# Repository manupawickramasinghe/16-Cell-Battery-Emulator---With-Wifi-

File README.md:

# 16 Cell Battery Emulator - With Wifi 
 Battery Emulator FOr research and testing

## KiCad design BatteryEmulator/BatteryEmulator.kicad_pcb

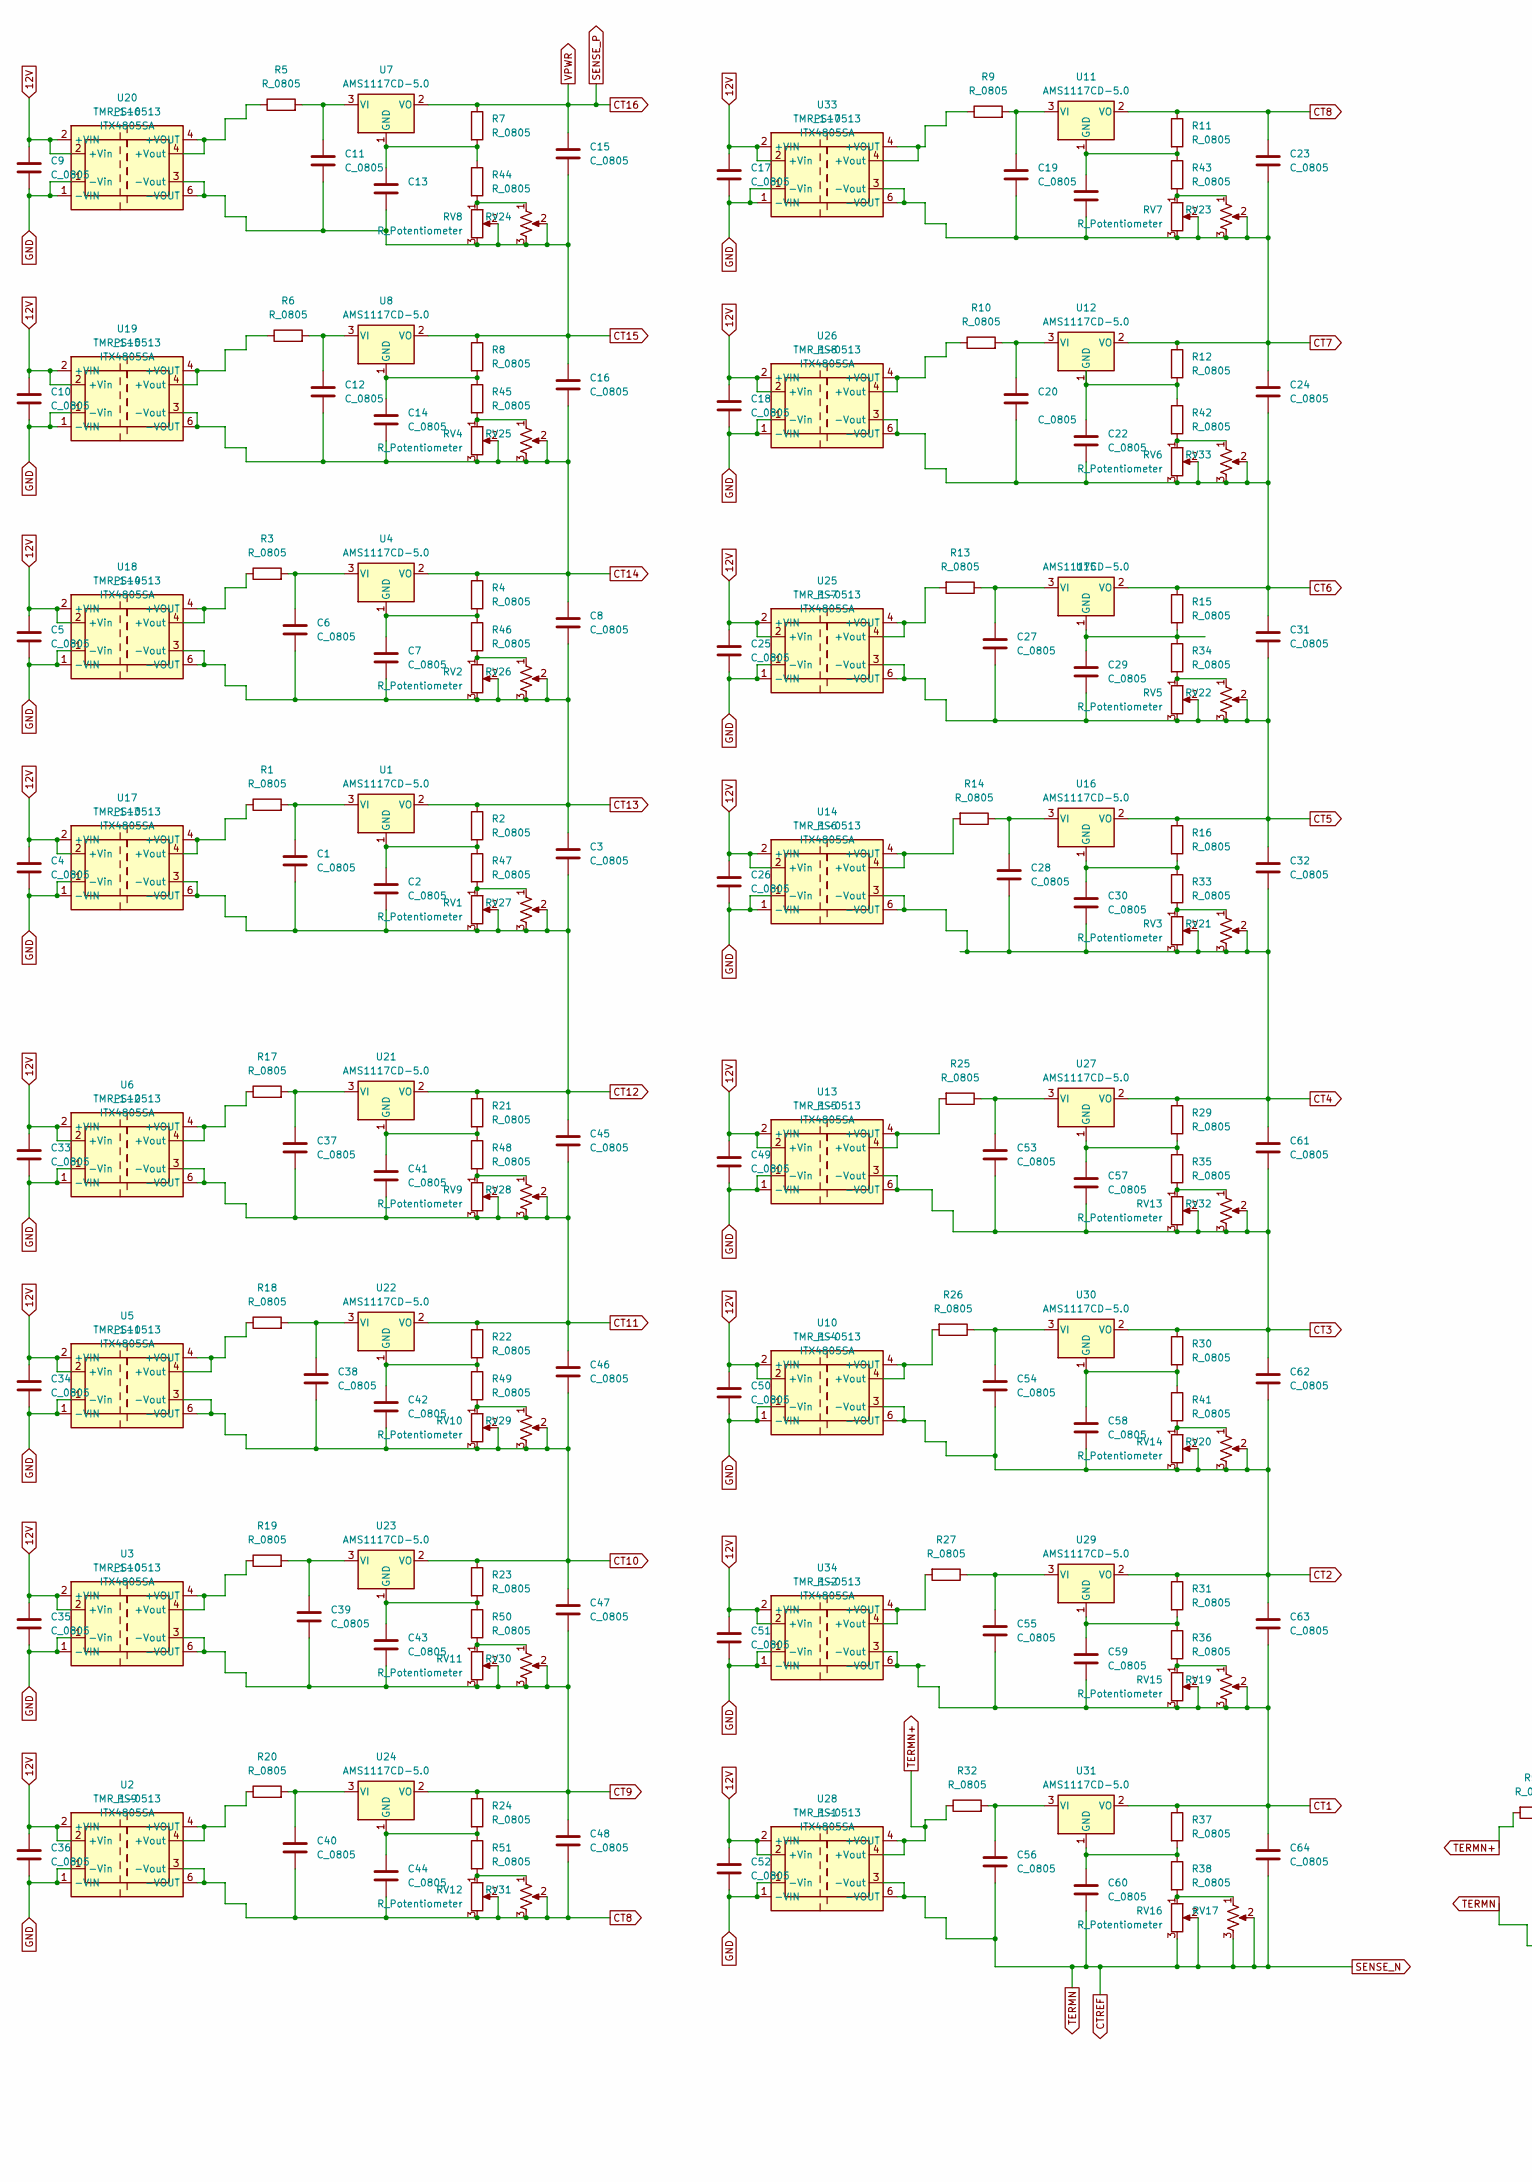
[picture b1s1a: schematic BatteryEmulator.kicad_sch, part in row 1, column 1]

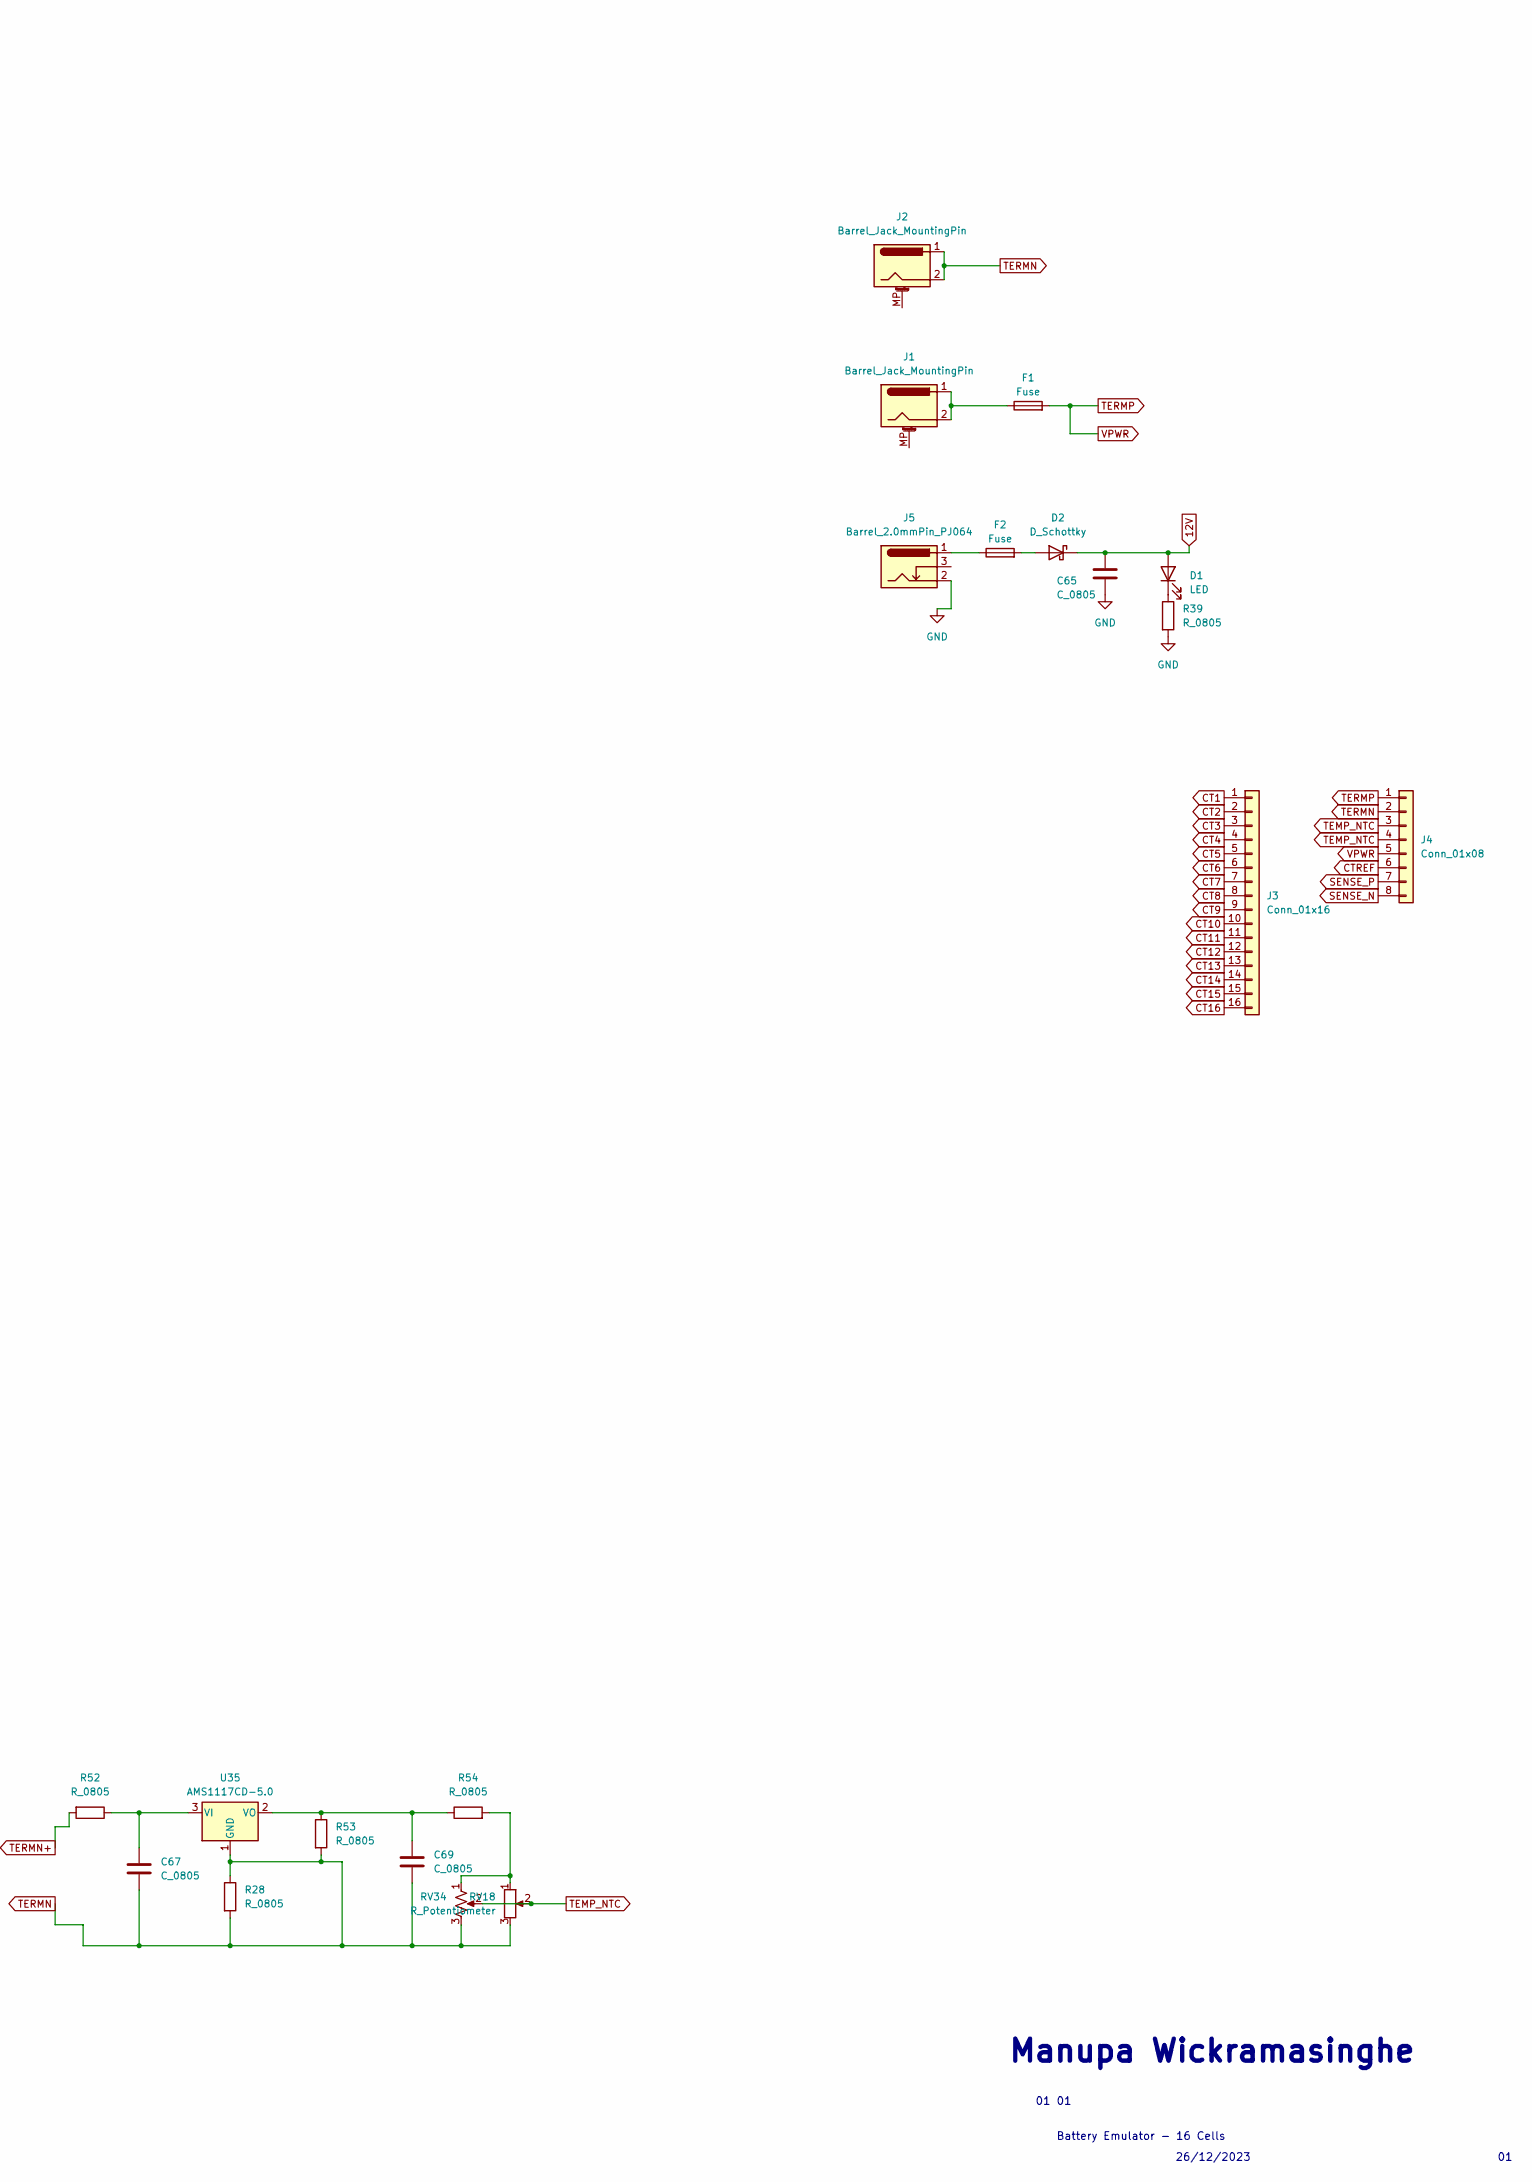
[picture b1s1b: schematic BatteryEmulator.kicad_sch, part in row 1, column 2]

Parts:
C1, C2, C3, C4, C5, C6, C7, C8, C9, C10, C11, C12, C13, C14, C15, C16, C17, C18, C19, C20, C21, C22, C23, C24, C25, C26, C27, C28, C29, C30, C31, C32, C33, C34, C35, C36, C37, C38, C39, C40, C41, C42, C43, C44, C45, C46, C47, C48, C49, C50, C51, C52, C53, C54, C55, C56, C57, C58, C59, C60, C61, C62, C63, C64, C65, C67, C69: C_0805; C_0805_2012Metric
D1: LED; LED_D3.0mm
D2: D_Schottky; R_1206_3216Metric
F1, F2: Fuse; R_1206_3216Metric
J1, J2: Barrel_Jack_MountingPin; Molex_KK-396_5273-02A_1x02_P3.96mm_Vertical
J3: Conn_01x16; PinHeader_1x16_P2.54mm_Vertical
J4: Conn_01x08; PinHeader_1x08_P2.54mm_Vertical
J5: Barrel_2.0mmPin_PJ064; BarrelJack_GCT_DCJ200-10-A_Horizontal; Part Number WQP-DC026M (2.0mm center pin)
PS1, PS2, PS4, PS5, PS6, PS7, PS8, PS9, PS10, PS11, PS12, PS13, PS14, PS15, PS16, PS17: ITX4805SA; Converter_DCDC_Murata_CRE1xxxxxxSC_THT
R1, R2, R3, R4, R5, R6, R7, R8, R9, R10, R11, R12, R13, R14, R15, R16, R17, R18, R19, R20, R21, R22, R23, R24, R25, R26, R27, R28, R29, R30, R31, R32, R33, R34, R35, R36, R37, R38, R39, R41, R42, R43, R44, R45, R46, R47, R48, R49, R50, R51, R52, R53, R54: R_0805; R_0805_2012Metric
RV1, RV2, RV3, RV4, RV5, RV6, RV7, RV8, RV9, RV10, RV11, RV12, RV13, RV14, RV15, RV16, RV18: R_Potentiometer; Potentiometer_Bourns_PTA6043_Single_Slide
RV17, RV19, RV20, RV21, RV22, RV23, RV24, RV25, RV26, RV27, RV28, RV29, RV30, RV31, RV32, RV33, RV34: R_Potentiometer_US; Potentiometer_Alps_RK09Y11_Single_Horizontal
U1, U4, U7, U8, U11, U12, U15, U16, U21, U22, U23, U24, U27, U29, U30, U31, U35: AMS1117CD-5.0; TO-252-3_TabPin2
U2, U3, U5, U6, U10, U13, U14, U17, U18, U19, U20, U25, U26, U28, U33, U34: TMR_1-0513; Converter_DCDC_TRACO_TMR-1-xxxx_Single_THT

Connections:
12V: C4.1, C5.1, C9.1, C10.1, C17.1, C18.1, C25.1, C26.1, C33.1, C34.1, C35.1, C36.1, C49.1, C50.1, C51.1, C52.1, C65.1, D1.2 (A), D2.1 (K), PS1.2 (+Vin), PS2.2 (+Vin), PS4.2 (+Vin), PS5.2 (+Vin), PS6.2 (+Vin), PS7.2 (+Vin), PS8.2 (+Vin), PS9.2 (+Vin), PS10.2 (+Vin), PS11.2 (+Vin), PS12.2 (+Vin), PS13.2 (+Vin), PS14.2 (+Vin), PS15.2 (+Vin), PS16.2 (+Vin), PS17.2 (+Vin), U2.2 (+VIN), U3.2 (+VIN), U5.2 (+VIN), U6.2 (+VIN), U10.2 (+VIN), U13.2 (+VIN), U14.2 (+VIN), U17.2 (+VIN), U18.2 (+VIN), U19.2 (+VIN), U20.2 (+VIN), U25.2 (+VIN), U26.2 (+VIN), U28.2 (+VIN), U33.2 (+VIN), U34.2 (+VIN)
CT1: C55.2, C59.2, C63.2, C64.1, J3.1, PS2.3 (-Vout), R37.1, RV15.2, RV15.3, RV19.2, RV19.3, U31.2 (VO), U34.6 (-VOUT)
CT2: C54.2, C58.2, C62.2, C63.1, J3.2, PS4.3 (-Vout), R31.1, RV14.2, RV14.3, RV20.2, RV20.3, U10.6 (-VOUT), U29.2 (VO)
CT3: C53.2, C57.2, C61.2, C62.1, J3.3, PS5.3 (-Vout), R30.1, RV13.2, RV13.3, RV32.2, RV32.3, U13.6 (-VOUT), U30.2 (VO)
CT4: C28.2, C30.2, C32.2, C61.1, J3.4, PS6.3 (-Vout), R29.1, RV3.2, RV3.3, RV21.2, RV21.3, U14.6 (-VOUT), U27.2 (VO)
CT5: C27.2, C29.2, C31.2, C32.1, J3.5, PS7.3 (-Vout), R16.1, RV5.2, RV5.3, RV22.2, RV22.3, U16.2 (VO), U25.6 (-VOUT)
CT6: C20.2, C22.2, C24.2, C31.1, J3.6, PS8.3 (-Vout), R15.1, RV6.2, RV6.3, RV33.2, RV33.3, U15.2 (VO), U26.6 (-VOUT)
CT7: C19.2, C21.2, C23.2, C24.1, J3.7, PS17.3 (-Vout), R12.1, RV7.2, RV7.3, RV23.2, RV23.3, U12.2 (VO), U33.6 (-VOUT)
CT8: C23.1, C40.2, C44.2, C48.2, J3.8, PS9.3 (-Vout), R11.1, RV12.2, RV12.3, RV31.2, RV31.3, U2.6 (-VOUT), U11.2 (VO)
CT9: C39.2, C43.2, C47.2, C48.1, J3.9, PS10.3 (-Vout), R24.1, RV11.2, RV11.3, RV30.2, RV30.3, U3.6 (-VOUT), U24.2 (VO)
CT10: C38.2, C42.2, C46.2, C47.1, J3.10, PS11.3 (-Vout), R23.1, RV10.2, RV10.3, RV29.2, RV29.3, U5.6 (-VOUT), U23.2 (VO)
CT11: C37.2, C41.2, C45.2, C46.1, J3.11, PS12.3 (-Vout), R22.1, RV9.2, RV9.3, RV28.2, RV28.3, U6.6 (-VOUT), U22.2 (VO)
CT12: C1.2, C2.2, C3.2, C45.1, J3.12, PS13.3 (-Vout), R21.1, RV1.2, RV1.3, RV27.2, RV27.3, U17.6 (-VOUT), U21.2 (VO)
CT13: C3.1, C6.2, C7.2, C8.2, J3.13, PS14.3 (-Vout), R2.1, RV2.2, RV2.3, RV26.2, RV26.3, U1.2 (VO), U18.6 (-VOUT)
CT14: C8.1, C12.2, C14.2, C16.2, J3.14, PS15.3 (-Vout), R4.1, RV4.2, RV4.3, RV25.2, RV25.3, U4.2 (VO), U19.6 (-VOUT)
CT15: C11.2, C13.2, C15.2, C16.1, J3.15, PS16.3 (-Vout), R8.1, RV8.2, RV8.3, RV24.2, RV24.3, U8.2 (VO), U20.6 (-VOUT)
CT16: C15.1, F1.2, J3.16, J4.1, J4.5, J4.7, R7.1, U7.2 (VO)
CTREF: C56.2, C60.2, C64.2, C67.2, C69.2, J2.1, J2.2, J4.2, J4.6, J4.8, PS1.3 (-Vout), R28.1, R28.2, R53.2, RV16.2, RV16.3, RV17.2, RV17.3, RV18.3, RV34.3, U28.6 (-VOUT), U35.1 (GND)
GND: C4.2, C5.2, C9.2, C10.2, C17.2, C18.2, C25.2, C26.2, C33.2, C34.2, C35.2, C36.2, C49.2, C50.2, C51.2, C52.2, C65.2, J5.2, PS1.1 (-Vin), PS2.1 (-Vin), PS4.1 (-Vin), PS5.1 (-Vin), PS6.1 (-Vin), PS7.1 (-Vin), PS8.1 (-Vin), PS9.1 (-Vin), PS10.1 (-Vin), PS11.1 (-Vin), PS12.1 (-Vin), PS13.1 (-Vin), PS14.1 (-Vin), PS15.1 (-Vin), PS16.1 (-Vin), PS17.1 (-Vin), R39.2, U2.1 (-VIN), U3.1 (-VIN), U5.1 (-VIN), U6.1 (-VIN), U10.1 (-VIN), U13.1 (-VIN), U14.1 (-VIN), U17.1 (-VIN), U18.1 (-VIN), U19.1 (-VIN), U20.1 (-VIN), U25.1 (-VIN), U26.1 (-VIN), U28.1 (-VIN), U33.1 (-VIN), U34.1 (-VIN)
unnamed: D1.1 (K), R39.1
unnamed: D2.2 (A), F2.2
unnamed: F1.1, J1.1, J1.2
unnamed: F2.1, J5.1
unnamed: PS2.4 (+Vout), R27.2, U34.4 (+VOUT)
unnamed: PS4.4 (+Vout), R26.2, U10.4 (+VOUT)
unnamed: PS5.4 (+Vout), R25.2, U13.4 (+VOUT)
unnamed: PS6.4 (+Vout), R14.2, U14.4 (+VOUT)
unnamed: PS7.4 (+Vout), R13.2, U25.4 (+VOUT)
unnamed: PS8.4 (+Vout), R10.1, U26.4 (+VOUT)
unnamed: PS9.4 (+Vout), R20.1, U2.4 (+VOUT)
unnamed: PS10.4 (+Vout), R19.1, U3.4 (+VOUT)
unnamed: PS11.4 (+Vout), R18.1, U5.4 (+VOUT)
unnamed: PS12.4 (+Vout), R17.1, U6.4 (+VOUT)
unnamed: PS13.4 (+Vout), R1.1, U17.4 (+VOUT)
unnamed: PS14.4 (+Vout), R3.1, U18.4 (+VOUT)
unnamed: PS15.4 (+Vout), R6.1, U19.4 (+VOUT)
unnamed: PS16.4 (+Vout), R5.1, U20.4 (+VOUT)
unnamed: PS17.4 (+Vout), R9.1, U33.4 (+VOUT)
unnamed: R33.2, RV3.1, RV21.1
unnamed: R34.2, RV5.1, RV22.1
unnamed: R35.2, RV13.1, RV32.1
unnamed: R36.2, RV15.1, RV19.1
unnamed: R38.2, RV16.1, RV17.1
unnamed: R41.2, RV14.1, RV20.1
unnamed: R42.2, RV6.1, RV33.1
unnamed: R43.2, RV7.1, RV23.1
unnamed: R44.2, RV8.1, RV24.1
unnamed: R45.2, RV4.1, RV25.1
unnamed: R46.2, RV2.1, RV26.1
unnamed: R47.2, RV1.1, RV27.1
unnamed: R48.2, RV9.1, RV28.1
unnamed: R49.2, RV10.1, RV29.1
unnamed: R50.2, RV11.1, RV30.1
unnamed: R51.2, RV12.1, RV31.1
unnamed: R54.2, RV18.1, RV34.1
unnamed: C2.1, R2.2, R47.1, U1.1 (GND)
unnamed: C1.1, R1.2, U1.3 (VI)
unnamed: C7.1, R4.2, R46.1, U4.1 (GND)
unnamed: C6.1, R3.2, U4.3 (VI)
unnamed: C13.1, R7.2, R44.1, U7.1 (GND)
unnamed: C11.1, R5.2, U7.3 (VI)
unnamed: C14.1, R8.2, R45.1, U8.1 (GND)
unnamed: C12.1, R6.2, U8.3 (VI)
unnamed: C21.1, R11.2, R43.1, U11.1 (GND)
unnamed: C19.1, R9.2, U11.3 (VI)
unnamed: C22.1, R12.2, R42.1, U12.1 (GND)
unnamed: C20.1, R10.2, U12.3 (VI)
unnamed: C29.1, R15.2, R34.1, U15.1 (GND)
unnamed: C27.1, R13.1, U15.3 (VI)
unnamed: C30.1, R16.2, R33.1, U16.1 (GND)
unnamed: C28.1, R14.1, U16.3 (VI)
unnamed: C41.1, R21.2, R48.1, U21.1 (GND)
unnamed: C37.1, R17.2, U21.3 (VI)
unnamed: C42.1, R22.2, R49.1, U22.1 (GND)
unnamed: C38.1, R18.2, U22.3 (VI)
unnamed: C43.1, R23.2, R50.1, U23.1 (GND)
unnamed: C39.1, R19.2, U23.3 (VI)
unnamed: C44.1, R24.2, R51.1, U24.1 (GND)
unnamed: C40.1, R20.2, U24.3 (VI)
unnamed: C57.1, R29.2, R35.1, U27.1 (GND)
unnamed: C53.1, R25.1, U27.3 (VI)
unnamed: C59.1, R31.2, R36.1, U29.1 (GND)
unnamed: C55.1, R27.1, U29.3 (VI)
unnamed: C58.1, R30.2, R41.1, U30.1 (GND)
unnamed: C54.1, R26.1, U30.3 (VI)
unnamed: C60.1, R37.2, R38.1, U31.1 (GND)
unnamed: C56.1, R32.2, U31.3 (VI)
unnamed: C67.1, R52.1, U35.3 (VI)
unnamed: C69.1, R53.1, R54.1, U35.2 (VO)
TEMP_NTC: J4.3, J4.4, RV18.2, RV34.2
TERMN+: PS1.4 (+Vout), R32.1, R52.2, U28.4 (+VOUT)

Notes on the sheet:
Battery Emulator - 16 Cells
Manupa Wickramasinghe
26/12/2023

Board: 2 copper layers, 212 parts (17 on the bottom side), 91 nets, no tracks yet.

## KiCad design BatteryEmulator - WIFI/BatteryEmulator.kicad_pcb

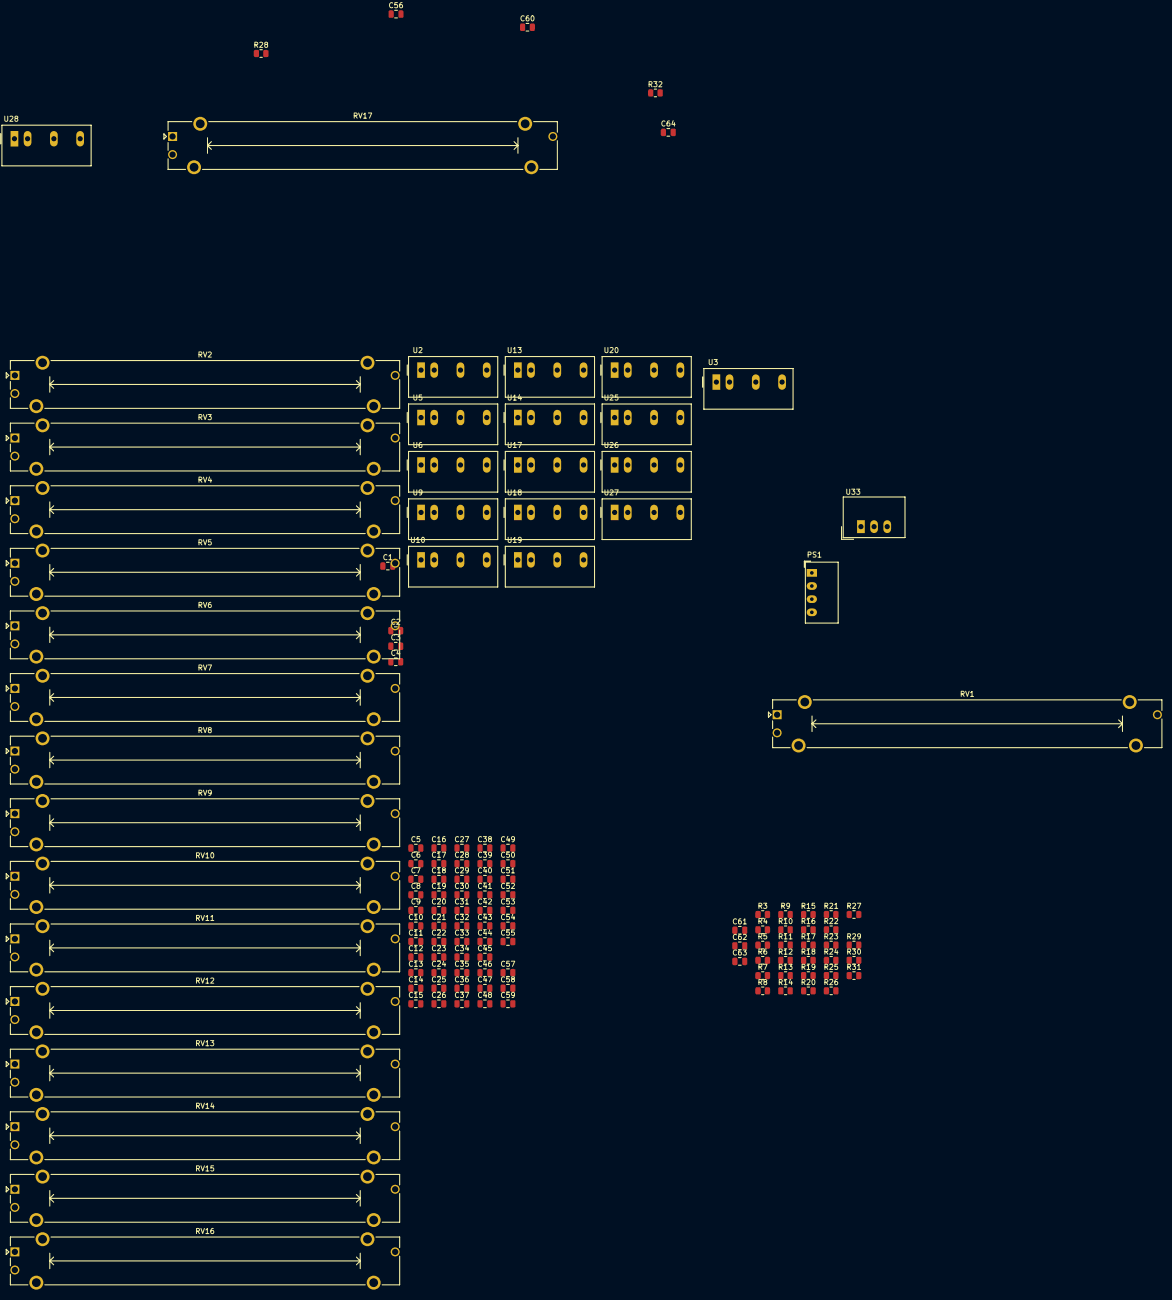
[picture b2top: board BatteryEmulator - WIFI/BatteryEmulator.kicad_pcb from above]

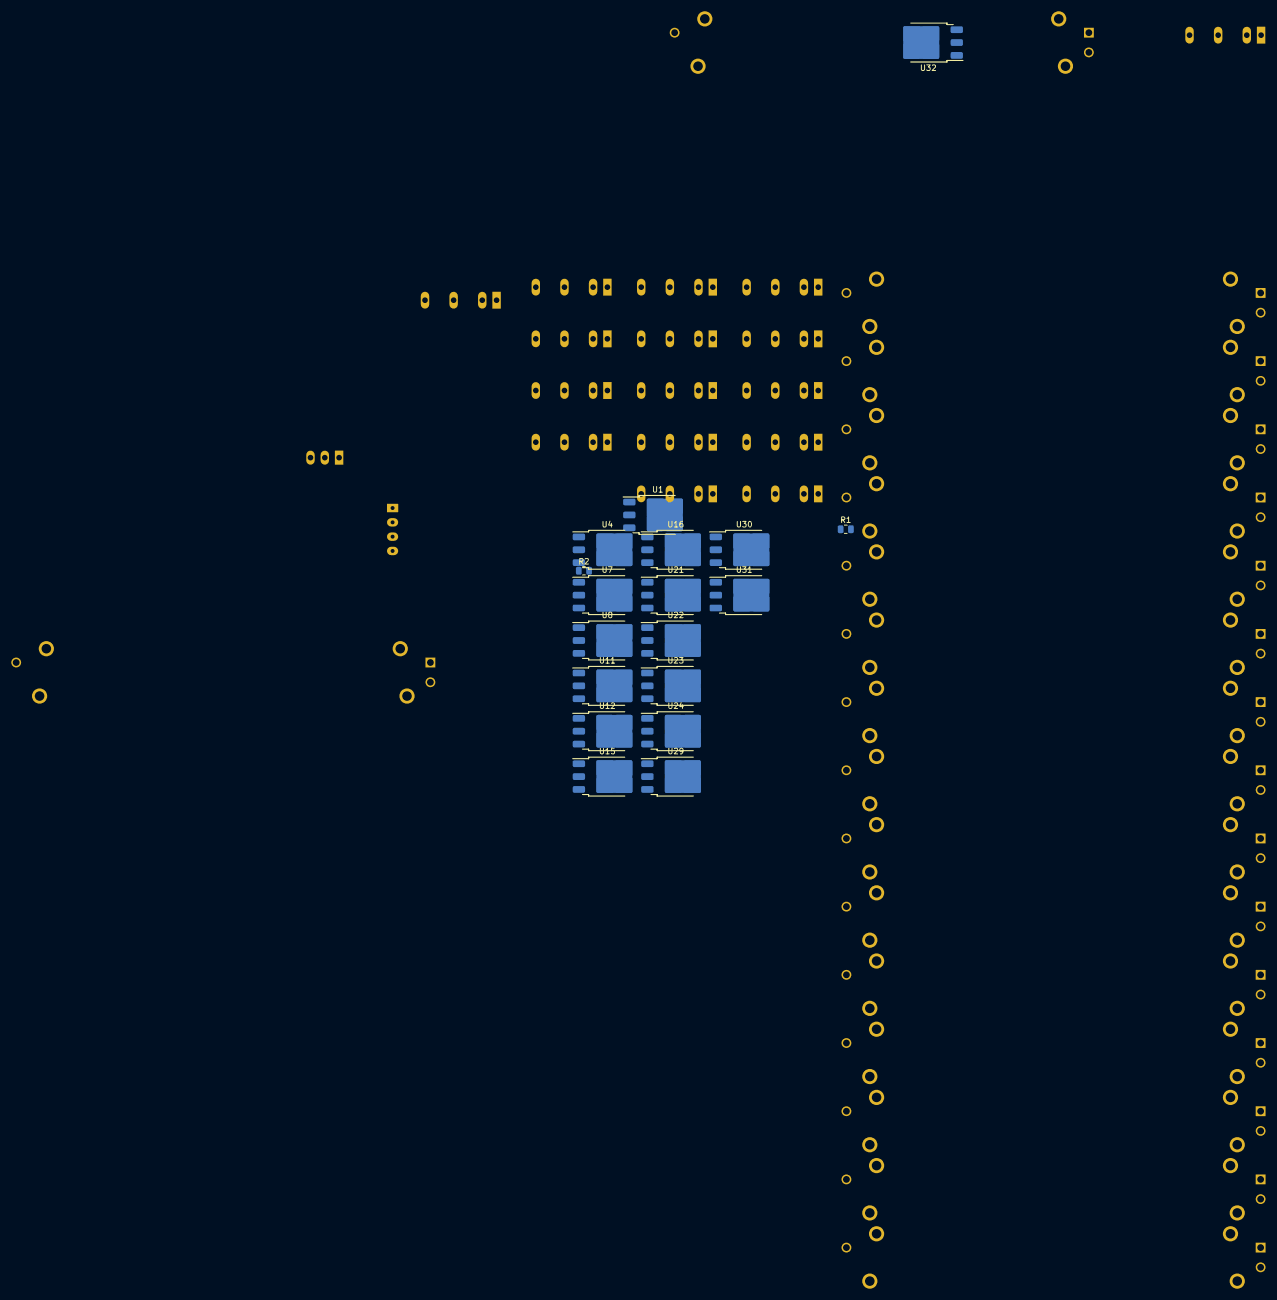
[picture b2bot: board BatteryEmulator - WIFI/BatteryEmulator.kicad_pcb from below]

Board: 2 copper layers, 147 parts (18 on the bottom side), 52 nets, no tracks yet.

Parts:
C1, C2, C3, C4, C5, C6, C7, C8, C9, C10, C11, C12, C13, C14, C15, C16, C17, C18, C19, C20, C21, C22, C23, C24, C25, C26, C27, C28, C29, C30, C31, C32, C33, C34, C35, C36, C37, C38, C39, C40, C41, C42, C43, C44, C45, C46, C47, C48, C49, C50, C51, C52, C53, C54, C55, C56, C57, C58, C59, C60, C61, C62, C63, C64: C_0805; C_0805_2012Metric
PS1: ITX4805SA; Converter_DCDC_Murata_CRE1xxxxxxSC_THT
R1, R2, R3, R4, R5, R6, R7, R8, R9, R10, R11, R12, R13, R14, R15, R16, R17, R18, R19, R20, R21, R22, R23, R24, R25, R26, R27, R28, R29, R30, R31, R32: R_0805; R_0805_2012Metric
RV1, RV2, RV3, RV4, RV5, RV6, RV7, RV8, RV9, RV10, RV11, RV12, RV13, RV14, RV15, RV16: R_Potentiometer; Potentiometer_Bourns_PTA6043_Single_Slide
RV17: R_Potentiometer_MountingPin; Potentiometer_Bourns_PTA6043_Single_Slide
U1, U4, U7, U8, U11, U12, U15, U16, U21, U22, U23, U24, U29, U30, U31, U32: AMS1117CD-5.0; TO-252-3_TabPin2
U2, U3, U5, U6, U9, U10, U13, U14, U17, U18, U19, U20, U25, U26, U27, U28: TMR_1-0513; Converter_DCDC_TRACO_TMR-1-xxxx_Single_THT
U33: TSR_1-24150; Converter_DCDC_TRACO_TSR-1_THT

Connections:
12V: C4.1, C5.1, C9.1, C10.1, C17.1, C18.1, C25.1, C26.1, C33.1, C34.1, C35.1, C36.1, C49.1, C50.1, C51.1, C52.1, U2.2 (+VIN), U3.2 (+VIN), U5.2 (+VIN), U6.2 (+VIN), U9.2 (+VIN), U10.2 (+VIN), U13.2 (+VIN), U14.2 (+VIN), U17.2 (+VIN), U18.2 (+VIN), U19.2 (+VIN), U20.2 (+VIN), U25.2 (+VIN), U26.2 (+VIN), U27.2 (+VIN), U28.2 (+VIN)
CT1: C55.2, C59.2, C63.2, C64.1, R27.2, R32.1, RV15.2, RV15.3, U27.6 (-VOUT), U32.2 (VO)
CT2: C54.2, C58.2, C62.2, C63.1, R26.2, R31.1, RV14.2, RV14.3, U26.6 (-VOUT), U31.2 (VO)
CT3: C53.2, C57.2, C61.2, C62.1, R25.2, R30.1, RV13.2, RV13.3, U25.6 (-VOUT), U30.2 (VO)
CT4: C28.2, C30.2, C32.2, C61.1, R14.2, R29.1, RV8.2, RV8.3, U14.6 (-VOUT), U29.2 (VO)
CT5: C27.2, C29.2, C31.2, C32.1, R13.2, R16.1, RV7.2, RV7.3, U13.6 (-VOUT), U16.2 (VO)
CT6: C20.2, C22.2, C24.2, C31.1, R10.2, R15.1, RV6.2, RV6.3, U10.6 (-VOUT), U15.2 (VO)
CT7: C19.2, C21.2, C23.2, C24.1, R9.2, R12.1, RV5.2, RV5.3, U9.6 (-VOUT), U12.2 (VO)
CT8: C23.1, C40.2, C44.2, C48.2, R11.1, R20.2, RV12.2, RV12.3, U11.2 (VO), U20.6 (-VOUT)
CT9: C39.2, C43.2, C47.2, C48.1, R19.2, R24.1, RV11.2, RV11.3, U19.6 (-VOUT), U24.2 (VO)
CT10: C38.2, C42.2, C46.2, C47.1, R18.2, R23.1, RV10.2, RV10.3, U18.6 (-VOUT), U23.2 (VO)
CT11: C37.2, C41.2, C45.2, C46.1, R17.2, R22.1, RV9.2, RV9.3, U17.6 (-VOUT), U22.2 (VO)
CT12: C1.2, C2.2, C3.2, C45.1, R1.2, R21.1, RV1.2, RV1.3, U3.6 (-VOUT), U21.2 (VO)
CT13: C3.1, C6.2, C7.2, C8.2, R2.1, R3.2, RV2.2, RV2.3, U1.2 (VO), U2.6 (-VOUT)
CT14: C8.1, C12.2, C14.2, C16.2, R4.1, R6.2, RV4.2, RV4.3, U4.2 (VO), U6.6 (-VOUT)
CT15: C11.2, C13.2, C15.2, C16.1, R5.2, R8.1, RV3.2, RV3.3, U5.6 (-VOUT), U8.2 (VO)
CT16: C15.1, R7.1, U7.2 (VO)
GND: C4.2, C5.2, C9.2, C10.2, C17.2, C18.2, C25.2, C26.2, C33.2, C34.2, C35.2, C36.2, C49.2, C50.2, C51.2, C52.2, U2.1 (-VIN), U3.1 (-VIN), U5.1 (-VIN), U6.1 (-VIN), U9.1 (-VIN), U10.1 (-VIN), U13.1 (-VIN), U14.1 (-VIN), U17.1 (-VIN), U18.1 (-VIN), U19.1 (-VIN), U20.1 (-VIN), U25.1 (-VIN), U26.1 (-VIN), U27.1 (-VIN), U28.1 (-VIN)
unnamed: C2.1, R2.2, RV1.1, U1.1 (GND)
unnamed: C1.1, R1.1, U1.3 (VI), U3.4 (+VOUT)
unnamed: C6.1, R3.1, U2.4 (+VOUT), U4.3 (VI)
unnamed: C7.1, R4.2, RV2.1, U4.1 (GND)
unnamed: C11.1, R5.1, U5.4 (+VOUT), U7.3 (VI)
unnamed: C12.1, R6.1, U6.4 (+VOUT), U8.3 (VI)
unnamed: C13.1, R7.2, RV3.1, U7.1 (GND)
unnamed: C14.1, R8.2, RV4.1, U8.1 (GND)
unnamed: C20.1, R10.1, U10.4 (+VOUT), U12.3 (VI)
unnamed: C21.1, R11.2, RV5.1, U11.1 (GND)
unnamed: C19.1, R9.1, U9.4 (+VOUT), U11.3 (VI)
unnamed: C22.1, R12.2, RV6.1, U12.1 (GND)
unnamed: C27.1, R13.1, U13.4 (+VOUT), U15.3 (VI)
unnamed: C28.1, R14.1, U14.4 (+VOUT), U16.3 (VI)
unnamed: C29.1, R15.2, RV7.1, U15.1 (GND)
unnamed: C30.1, R16.2, RV8.1, U16.1 (GND)
unnamed: C37.1, R17.1, U17.4 (+VOUT), U21.3 (VI)
unnamed: C38.1, R18.1, U18.4 (+VOUT), U22.3 (VI)
unnamed: C39.1, R19.1, U19.4 (+VOUT), U23.3 (VI)
unnamed: C40.1, R20.1, U20.4 (+VOUT), U24.3 (VI)
unnamed: C41.1, R21.2, RV9.1, U21.1 (GND)
unnamed: C42.1, R22.2, RV10.1, U22.1 (GND)
unnamed: C43.1, R23.2, RV11.1, U23.1 (GND)
unnamed: C44.1, R24.2, RV12.1, U24.1 (GND)
unnamed: C53.1, R25.1, U25.4 (+VOUT), U29.3 (VI)
unnamed: C54.1, R26.1, U26.4 (+VOUT), U30.3 (VI)
unnamed: C55.1, R27.1, U27.4 (+VOUT), U31.3 (VI)
unnamed: RV16.2, RV16.3
unnamed: C57.1, R29.2, RV13.1, U29.1 (GND)
unnamed: C58.1, R30.2, RV14.1, U30.1 (GND)
unnamed: C59.1, R31.2, RV15.1, U31.1 (GND)
unnamed: C60.1, R32.2, RV16.1, RV17.1, U32.1 (GND)
TERMN: C56.2, C60.2, C64.2, R28.2, RV17.2, RV17.3, U28.6 (-VOUT)
TERMN-: C56.1, R28.1, U28.4 (+VOUT), U32.3 (VI)

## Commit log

2023-12-25 PCB Incomplete
2023-12-26 Complete Schematics of analog version
2023-12-30 uPLOADS
2024-01-10 Backup
2024-03-23 Schematics are finished.
    Need refactoring
